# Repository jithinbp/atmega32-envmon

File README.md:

# ATMEGA32 based environment monitor

## Features

+ ATMEGA32
+ 16 character display. dual row
+ MQ-2
+ MQ-135
+ Ports for 2 I2C sensors ( BMP280 )

### schematic

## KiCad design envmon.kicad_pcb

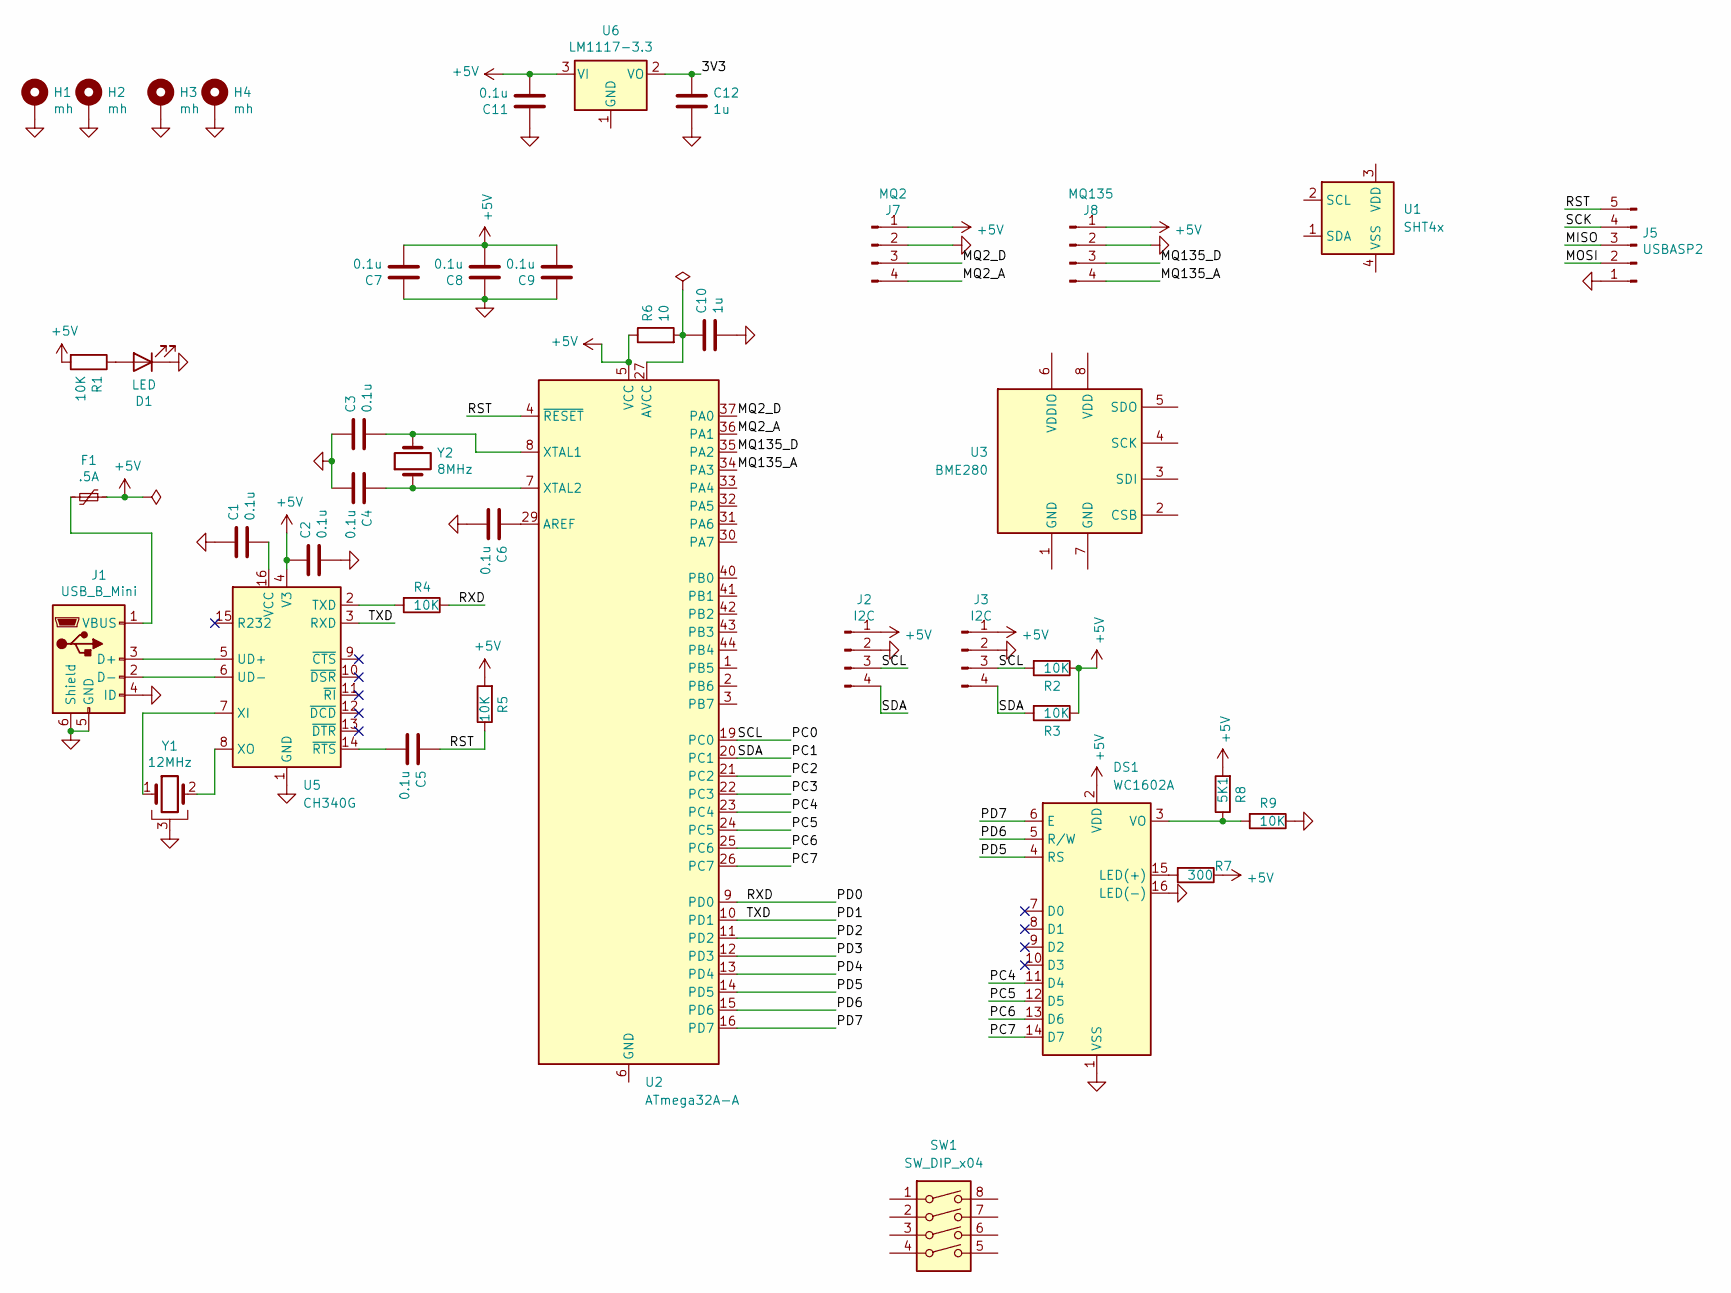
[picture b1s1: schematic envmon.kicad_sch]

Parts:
C1, C2, C3, C4, C5, C6, C7, C8, C9, C11: 0.1u; C_0805_2012Metric
C10, C12: 1u; C_0805_2012Metric
D1: LED; LED_0805_2012Metric
DS1: WC1602A
F1: .5A; Fuse_1812_4532Metric
H1, H2, H3, H4: mh; MountingHole_3.2mm_M3_DIN965
J1: USB_B_Mini; USB_Mini-B_Wuerth_65100516121_Horizontal
J2, J3: I2C; PinSocket_1x04_P2.54mm_Vertical
J5: USBASP2; PinHeader_1x05_P2.54mm_Vertical
J7: MQ2; PinSocket_1x04_P2.54mm_Vertical
J8: MQ135; PinSocket_1x04_P2.54mm_Vertical
R1, R2, R3, R4, R5, R9: 10K; R_0805_2012Metric
R6: 10; R_0805_2012Metric
R7: 300; R_0805_2012Metric
R8: 5K1; R_0805_2012Metric
SW1: SW_DIP_x04; MountingHole_3.2mm_M3_DIN965
U1: SHT4x; Sensirion_DFN-4_1.5x1.5mm_P0.8mm_SHT4x_NoCentralPad
U2: ATmega32A-A; TQFP-44_10x10mm_P0.8mm
U3: BME280; Bosch_LGA-8_2.5x2.5mm_P0.65mm_ClockwisePinNumbering
U5: CH340G; SOIC-16_3.9x9.9mm_P1.27mm
U6: LM1117-3.3; SOT-223-3_TabPin2
Y1: 12MHz; Crystal_HC49-4H_Vertical
Y2: 8MHz; Crystal_HC49-4H_Vertical

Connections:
+5V: C2.1, C7.2, C8.2, C9.2, C11.2, DS1.2 (VDD), F1.1, J2.1, J3.1, J7.1, J8.1, R1.2, R2.1, R3.1, R5.2, R6.1, R7.1, R8.2, U2.5 (VCC), U2.17 (VCC), U2.38 (VCC), U5.4 (V3), U6.3 (VI)
/3V3: C12.1, U6.2 (VO)
/MISO: J5.3
/MOSI: J5.2
/MQ2_A: J7.4, U2.36 (PA1)
/MQ2_D: J7.3, U2.37 (PA0)
/MQ135_A: J8.4, U2.34 (PA3)
/MQ135_D: J8.3, U2.35 (PA2)
/PC0: J2.3, J3.3, R2.2, U2.19 (PC0)
/PC1: J2.4, J3.4, R3.2, U2.20 (PC1)
/PC2: U2.21 (PC2)
/PC3: U2.22 (PC3)
/PC4: DS1.11 (D4), U2.23 (PC4)
/PC5: DS1.12 (D5), U2.24 (PC5)
/PC6: DS1.13 (D6), U2.25 (PC6)
/PC7: DS1.14 (D7), U2.26 (PC7)
/PD0: R4.1, U2.9 (PD0)
/PD1: U2.10 (PD1), U5.3 (RXD)
/PD2: U2.11 (PD2)
/PD3: U2.12 (PD3)
/PD4: U2.13 (PD4)
/PD5: DS1.4 (RS), U2.14 (PD5)
/PD6: DS1.5 (R/W), U2.15 (PD6)
/PD7: DS1.6 (E), U2.16 (PD7)
/RST: C5.1, J5.5, R5.1, U2.4 (~RESET)
/SCK: J5.4
GND: C1.1, C2.2, C3.1, C4.2, C6.2, C7.1, C8.1, C9.1, C10.2, C11.1, C12.2, D1.1 (K), DS1.1 (VSS), DS1.16 (LED(-)), H1.1, H2.1, H3.1, H4.1, J1.4 (ID), J1.5 (GND), J1.6 (Shield), J2.2, J3.2, J5.1, J7.2, J8.2, R9.1, U5.1 (GND), Y1.3
unnamed: D1.2 (A), R1.1
unnamed: DS1.15 (LED(+)), R7.2
unnamed: DS1.3 (VO), R8.1, R9.2
unnamed: J1.3 (D+), U5.5 (UD+)
unnamed: J1.2 (D-), U5.6 (UD-)
unnamed: F1.2, J1.1 (VBUS)
unnamed: C6.1, U2.29 (AREF)
unnamed: C10.1, R6.2, U2.27 (AVCC)
unnamed: U2.6 (GND), U2.18 (GND), U2.28 (GND), U2.39 (GND)
unnamed: C3.2, U2.8 (XTAL1), Y2.2
unnamed: C4.1, U2.7 (XTAL2), Y2.1
unnamed: R4.2, U5.2 (TXD)
unnamed: C1.2, U5.16 (VCC)
unnamed: U5.7 (XI), Y1.1
unnamed: U5.8 (XO), Y1.2
unnamed: C5.2, U5.14 (~RTS)

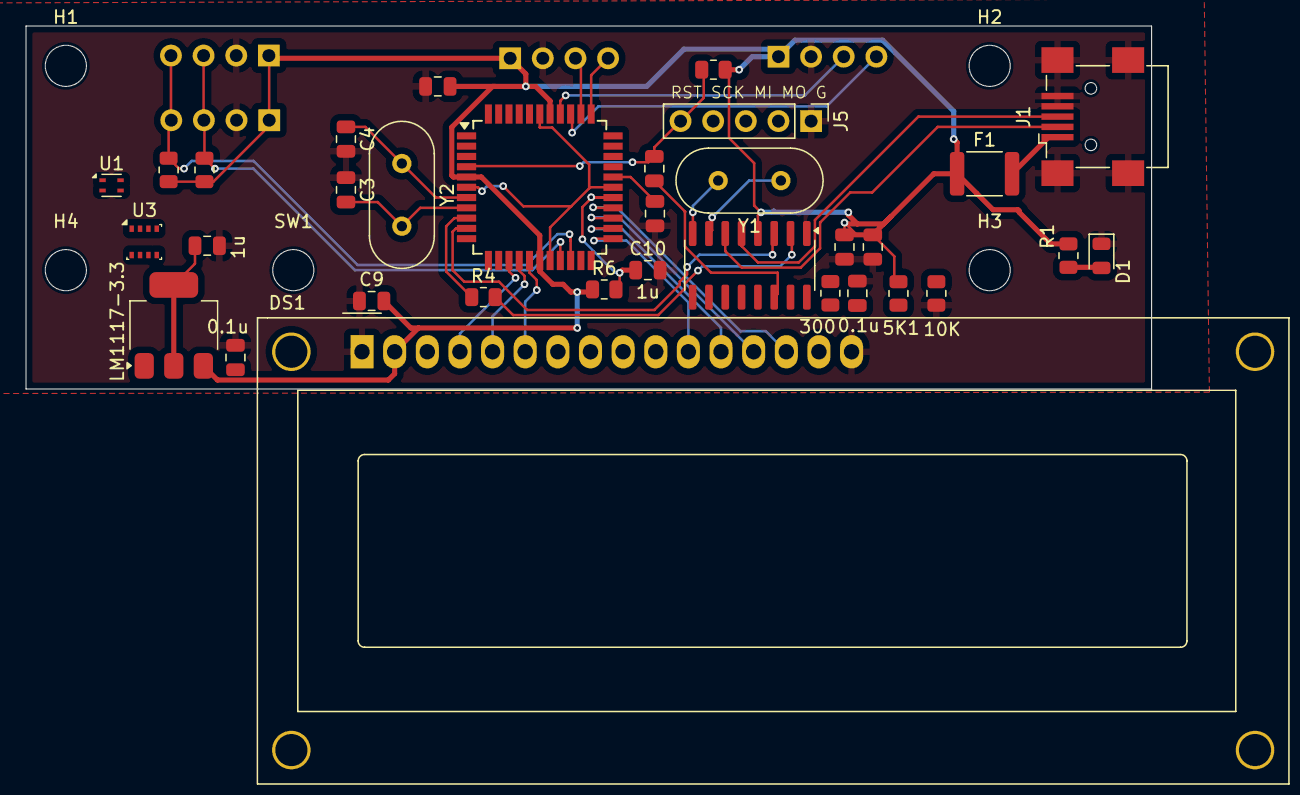
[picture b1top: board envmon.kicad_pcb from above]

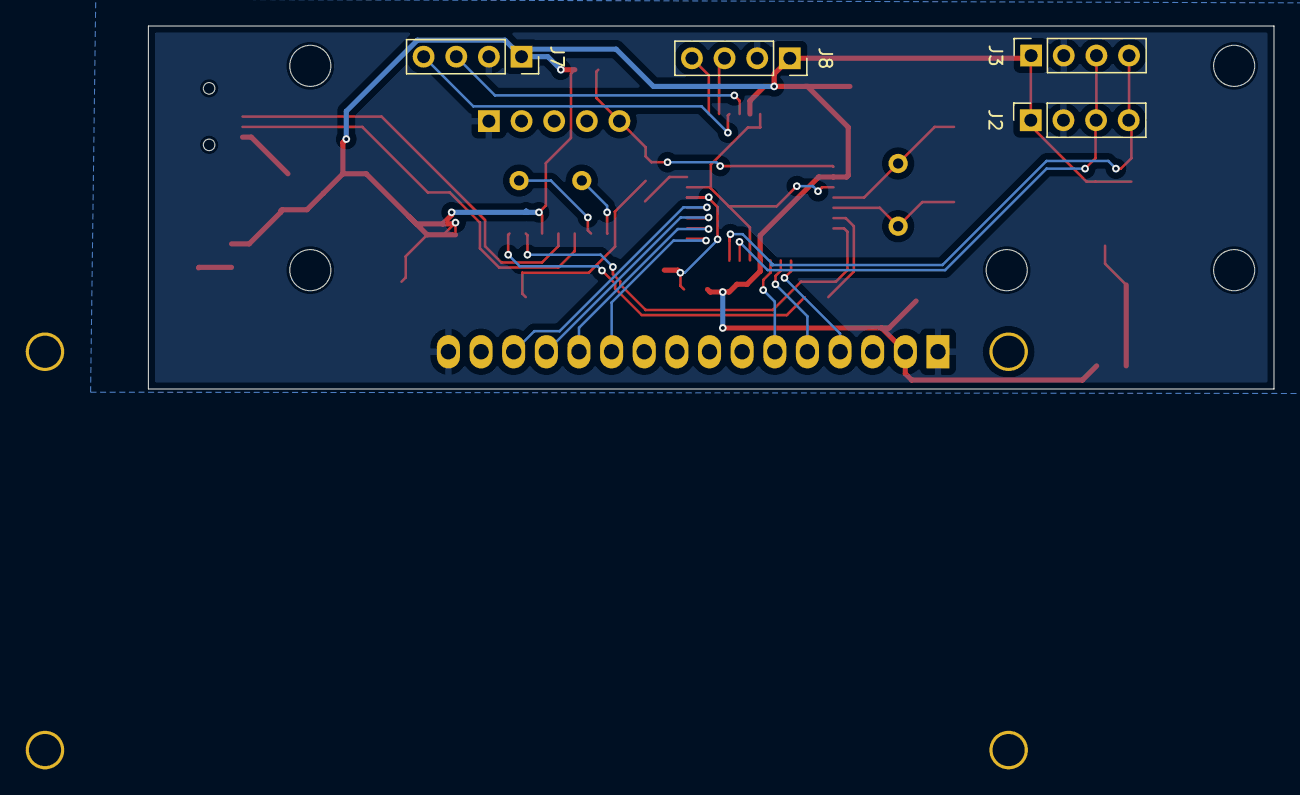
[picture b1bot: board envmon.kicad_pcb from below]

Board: 2 copper layers, 87.6 x 28.2 mm, 42 parts (4 on the bottom side), 35 nets.

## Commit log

2024-06-19 add schema photo
